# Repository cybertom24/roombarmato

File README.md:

# roombarmato

A repo to make a military version of the robotic vacuum cleaner Roomba

### TODO

#### PCB

- (OK) Posiziona fori di montaggio
- (OK) Trova valori per i condensatori del regolatore da 3.3V
- (OK) Controlla che il package dei componenti corrisponda
- (OK) Completa file ordine
- (OK) Modifica AK500
- (OK) Controlla funzionamento amplificatore audio
- (OK) Piano di massa in bottom e piano +12V in top

#### Arduino code

- (OK ?) Risolvi problema del blocco per colpa dei messaggi
- (OK) Aggiungi stop automatico dopo 2 secondi di assenza di messaggi
- Aggiungi controllo tensione della batteria e blocco di tutto quando si scende sotto i ~10.5V
- Completa comandi
- (OK) Aggiungi sistema di sincronizzazione ESP-arduino

##### Funzionalità

- (OK) Apri/Chiudi coperchio
- (OK) Spegni canne con millis() e non delay()
- (OK) Muovi
- (OK) Spegni motori dopo tot secondi di assenza messaggi
- (OK) Spegni tutto con disconnessione
- (OK) Accendi/Spegni occhi
- (OK) Controllo musica
- (OK) Controllo livello batteria
- (OK) Invio errore di lancio (perchè coperchio chiuso)
- (OK) Invio errore troppi messaggi
- Messaggio multiplo per accensione canne
- (OK) Invio stato batteria
- (OK) Invio stato coperchio

### ESP code

- Aggiungi sistema di sincronizzazione
- Aggiungi sistema di mantenimento di messaggi in modo da inviarne uno per volta

#### App

(OK) Semplifica algoritmo di gestione potenza dei motori

### Help

#### Comandi git

- Per impacchettare i file modificati: git add .
- Per assegnare il nome: git commit -m "nome alla modifica"
- Per caricare su internet: git push

- Per scaricare: git pull

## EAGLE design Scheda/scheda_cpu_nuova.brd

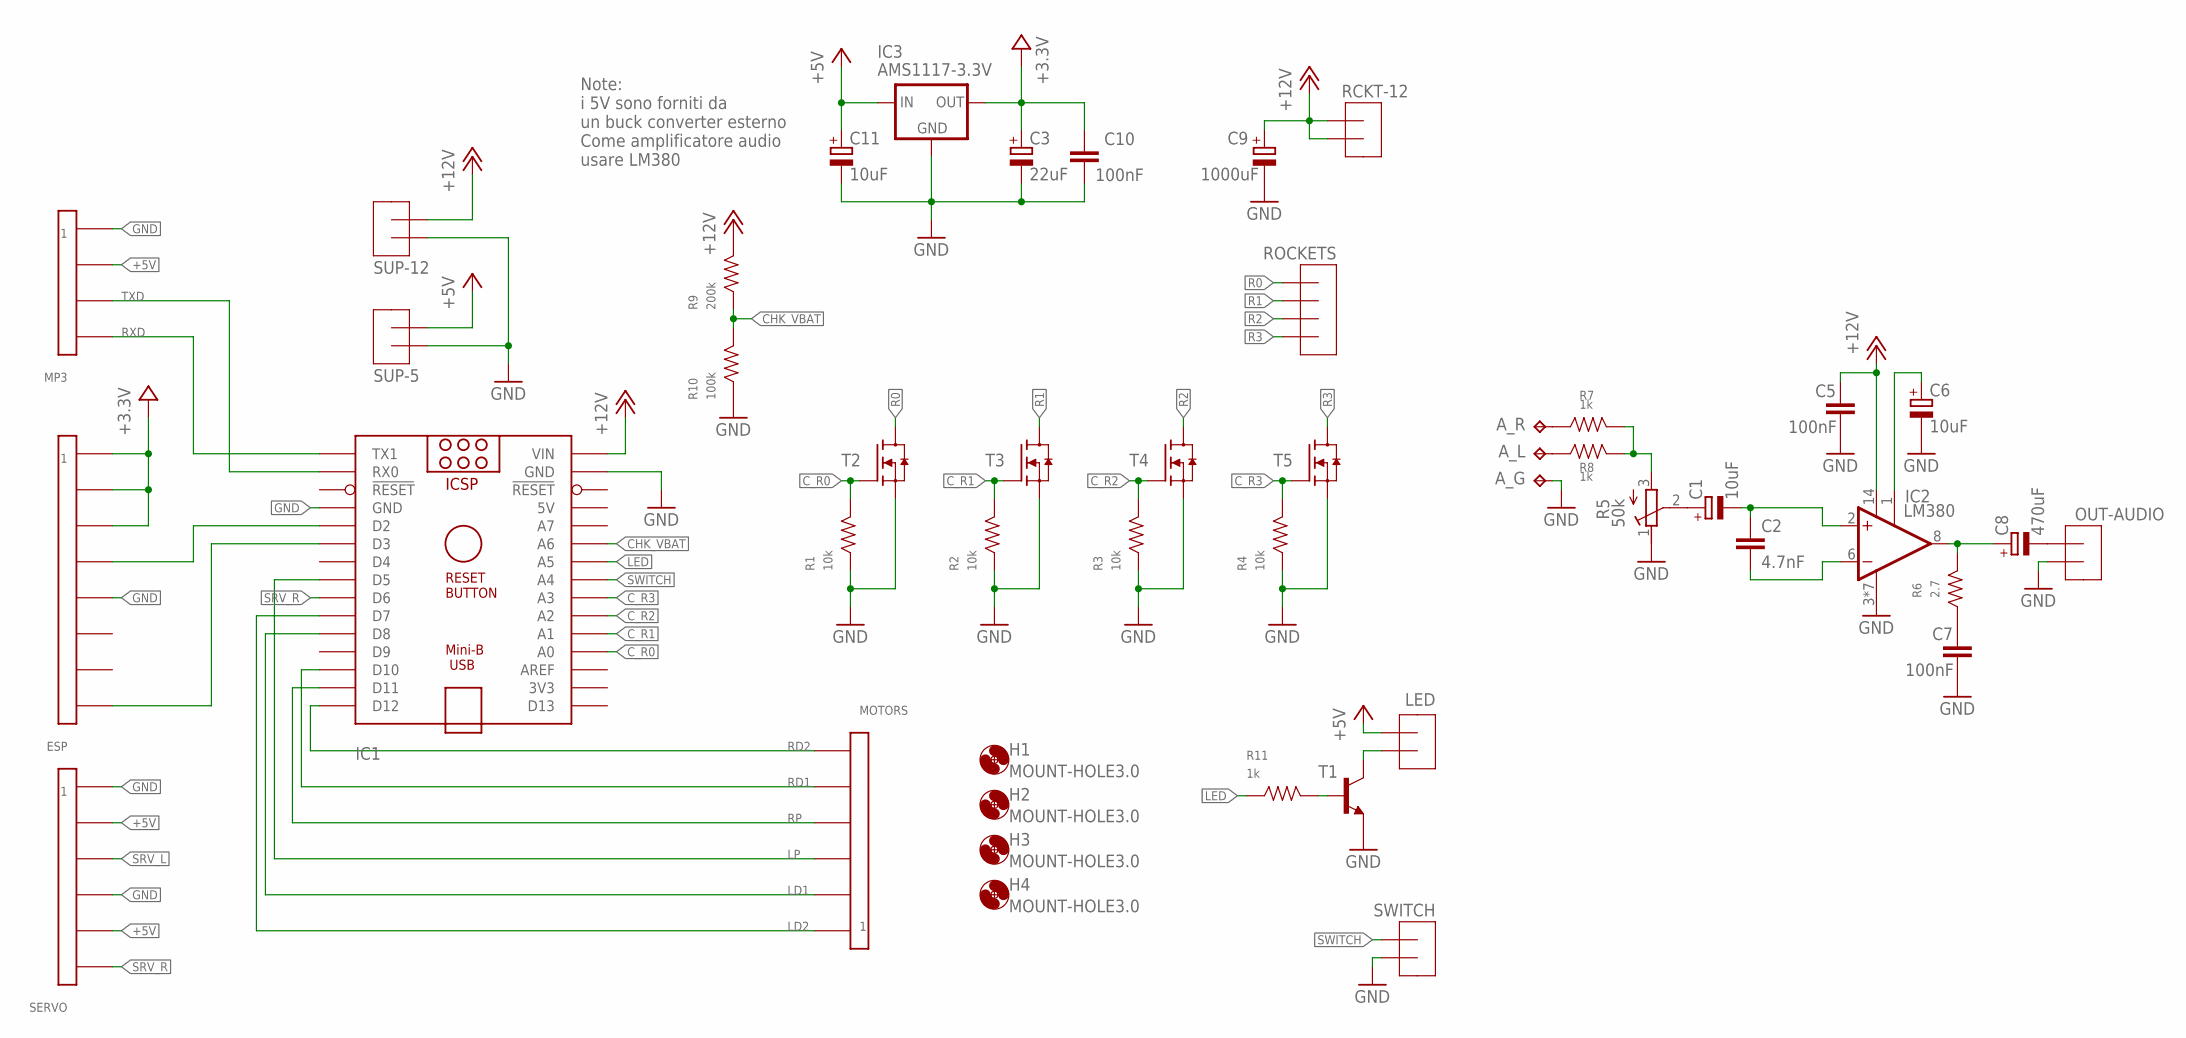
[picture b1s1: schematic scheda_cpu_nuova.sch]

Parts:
A_G: TPTP15SQ; TP15SQ
A_L: TPTP15SQ; TP15SQ
A_R: TPTP15SQ; TP15SQ
C1, C6, C11: 10uF; E2-4
C2: 4.7nF; C1206
C3: 22uF; E2-4
C5, C7, C10: 100nF; C1206
C8: 470uF; E3,5-8
C9: 1000uF; E3,5-10
ESP: CONNECTOR-82X4-CONNECTOR; 2X4-CONNECTOR
H1, H2, H3, H4: MOUNT-HOLE3.0; 3,0
IC1: ARDUINO-NANO; ARDUINO_NANO
IC2: LM380; DIL14
IC3: AMS1117-3.3V; SOT223
LED: MORSETTIERE-2
MOTORS: CONNECTOR-6; 1X6-CONNECTOR
MP3: CONNECTOR-4; 1X4-CONNECTOR
OUT-AUDIO: MORSETTIERE-2
R1, R2, R3, R4: 10k; 1206-RESISTOR
R5: 50k; RTRIM3314J
R6: 2.7; 1206-RESISTOR
R7, R8, R11: 1k; 1206-RESISTOR
R9: 200k; 1206-RESISTOR
R10: 100k; 1206-RESISTOR
RCKT-12: MORSETTIERE-2
ROCKETS: MORSETTIERE-4
SERVO: CONNECTOR-6; 1X6-CONNECTOR
SUP-5, SUP-12: MORSETTIERE-2
SWITCH: MORSETTIERE-2
T1: BC-817; SOT-23
T2, T3, T4, T5: MCU80N03A; D-PAK_TO252AA

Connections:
5V: IC1.12 (5V)
+3.3V: C3.+, C10.1, ESP.P$1, ESP.P$2, ESP.P$3, IC3.2 (OUT)
+5V: C11.+, IC3.3 (IN), LED.A, MP3.P$2, SERVO.P$2, SERVO.P$5, SUP-5.A
+12V: C5.1, C9.+, IC1.15 (VIN), IC2.14 (VSS), R9.P$2, RCKT-12.A, RCKT-12.B, SUP-12.A
CHK_VBAT: IC1.10 (A6), R9.P$1, R10.P$2
C_R0: IC1.4 (A0), R1.P$2, T2.1 (G)
C_R1: IC1.5 (A1), R2.P$2, T3.1 (G)
C_R2: IC1.6 (A2), R3.P$2, T4.1 (G)
C_R3: IC1.7 (A3), R4.P$2, T5.1 (G)
GND: A_G.TP, C3.-, C5.2, C6.-, C7.2, C9.-, C10.2, C11.-, ESP.P$5, IC1.14 (GND), IC1.19 (GND), IC2.3 (GND), IC2.4 (GND), IC2.5 (GND), IC2.7 (GND), IC2.10 (GND), IC2.11 (GND), IC2.12 (GND), IC3.1 (GND), MP3.P$1, OUT-AUDIO.A, R1.P$1, R2.P$1, R3.P$1, R4.P$1, R5.1 (E), R10.P$1, SERVO.P$1, SERVO.P$4, SUP-5.B, SUP-12.B, SWITCH.A, T1.P$1 (E), T2.3 (S), T3.3 (S), T4.3 (S), T5.3 (S)
IN_AUDIO: R5.3 (A), R7.P$2, R8.P$2
LD1: IC1.26 (D8), MOTORS.P$2
LD2: IC1.25 (D7), MOTORS.P$1
LED: IC1.9 (A5), R11.P$1
LP: IC1.23 (D5), MOTORS.P$3
unnamed: ESP.P$8, IC1.21 (D3)
unnamed: LED.B, T1.P$3 (C)
unnamed: R11.P$2, T1.P$2 (B)
unnamed: ESP.P$4, IC1.20 (D2)
unnamed: C1.+, R5.2 (S)
unnamed: C1.-, C2.1, IC2.2 (+IN)
unnamed: C2.2, IC2.6 (-IN)
unnamed: C6.+, IC2.1 (BYPASS)
unnamed: C7.1, R6.P$1
unnamed: C8.+, IC2.8 (OUT), R6.P$2
unnamed: C8.-, OUT-AUDIO.B
unnamed: A_R.TP, R7.P$1
unnamed: A_L.TP, R8.P$1
R0: ROCKETS.D, T2.4 (D)
R1: ROCKETS.C, T3.4 (D)
R2: ROCKETS.B, T4.4 (D)
R3: ROCKETS.A, T5.4 (D)
RD1: IC1.28 (D10), MOTORS.P$5
RD2: IC1.30 (D12), MOTORS.P$6
RP: IC1.29 (D11), MOTORS.P$4
RXD: IC1.16 (TX1), MP3.P$4
SRV_L: SERVO.P$3
SRV_R: IC1.24 (D6), SERVO.P$6
SWITCH: IC1.8 (A4), SWITCH.B
TXD: IC1.17 (RX0), MP3.P$3

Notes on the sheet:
Note: i 5V sono forniti da un buck converter esterno Come amplificatore audio usare LM380

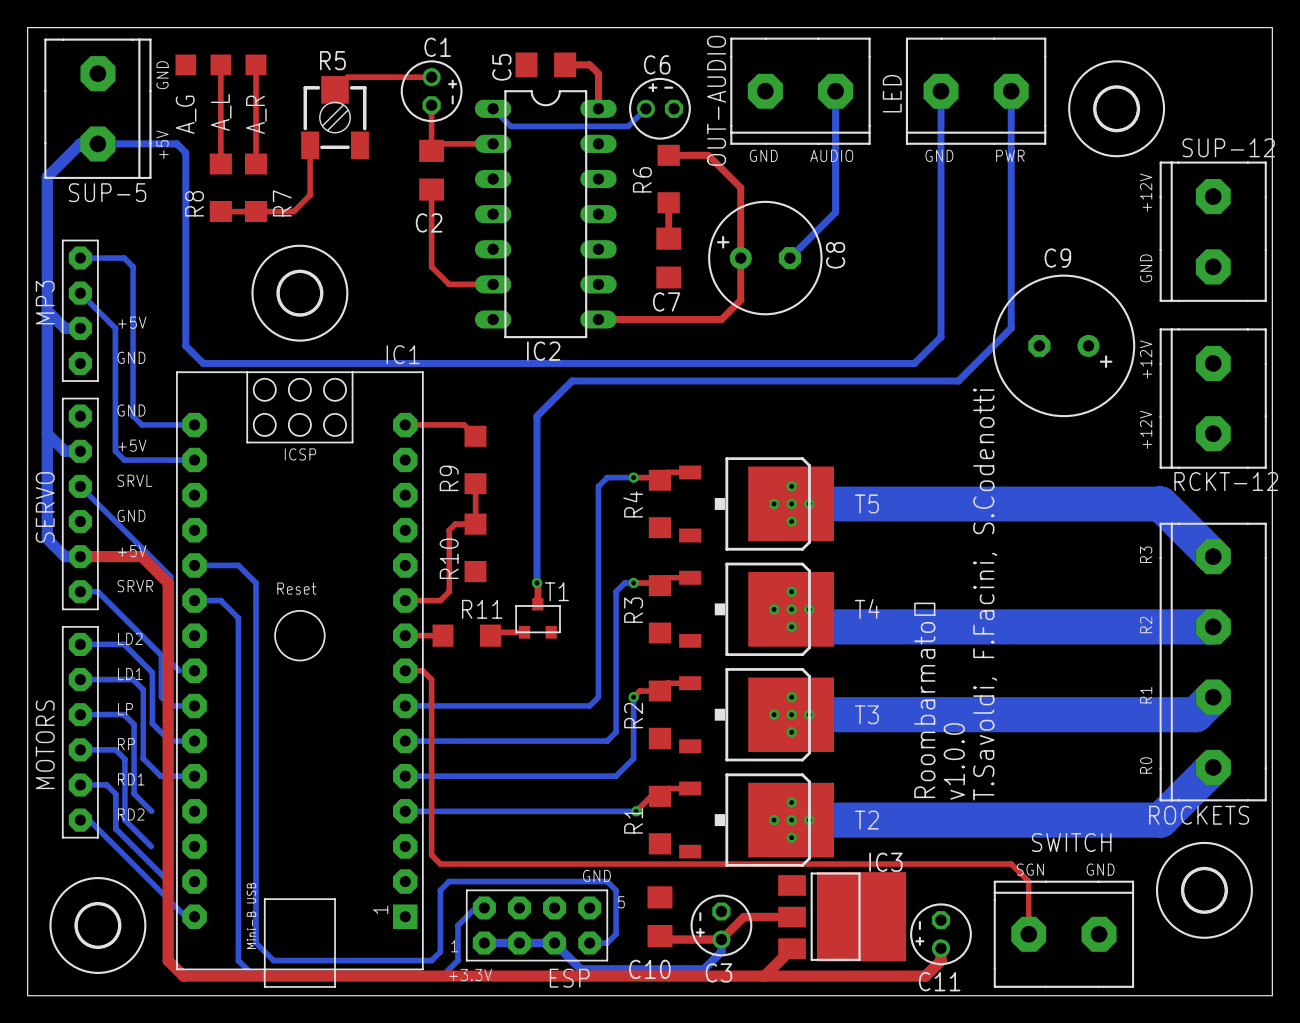
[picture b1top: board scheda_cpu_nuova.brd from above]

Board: 2 copper layers, 90.0 x 70.0 mm, 47 parts (0 on the bottom side), 38 nets.

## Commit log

2022-07-03 update with old files
2022-07-16 varie robe
2022-07-17 prova 2
2022-07-17 aggiunto cad canna per realizzazione prototipo n°2
2022-11-12 creata la libreria roombarmato_eagle_lib che verrà usata per tenere tutti i componenti presenti sulla scheda, aggiunti regolatori di tensione per la generazione di +5v e +3.3
2022-12-13 creato il pcb di prova
2023-01-14 modificato il sistema di accensione
2023-01-24 completato pcb con lm380
2023-01-24 creato file excel ordine
2023-01-25 aggiunta TODO in README.md
2023-01-25 Modificato TODO list in README
2023-01-25 aggiunte etichette su pcb
2023-01-25 aggiunti bat script per velocizzare push e pull
2023-02-10 create le cartelle test e ex
2023-02-28 modificato pcb
2023-03-11 modificato leggermente pcb, cambiato package lm380
2023-04-04 sistemato pcb
2023-04-04 quasi completato foglio ordine, da sistemare package condensatori (cambiare da 30x50 a 1206)
2023-04-05 sistemato pcb e ordine
2023-04-06 modificato todo
2023-04-06 completato PCB
2023-05-13 modificate varie robe
2023-05-13 modificati razzi
2023-06-04 modificati razzetti
2023-06-04 sistemata roba
2023-06-04 aggiunta file cad
2023-06-04 spostato cartella razzetti
2023-06-07 Sistemato progetti esp-code e arduino-code
2023-06-07 aggiunta libreria per TCP
2023-06-26 inseriti attacchi per servomotore e sistemato assembly finale sdw
2023-07-22 modifcato roba esp
2023-07-22 Crea cartella RoombaCode
2023-07-23 sistemato crash esp
2023-07-24 esp pronto all'uso; aggiunto funzioni ad arduino
2023-07-24 rimosso joystick_support (inutile)
2023-07-24 creato file algoritmo per code
2023-07-24 ampliato arduino-code
2023-07-24 creato file contenente tutti i comandi
2023-07-25 piccola modifica
2023-07-26 sistemato problema PWM
2023-07-27 modificato esp code
2023-07-27 Boh 5
2023-07-28 provando a sistemare comunicazione esp-arduino
2023-08-02 aggiungendo ECC alla comunicazione ESP-Arduino
2023-08-02 perSavo
2023-08-03 creando SecureSerial
2023-08-03 completando SecureSerial
2023-08-14 tentativi per migliorare connessione esp-arduino
2023-08-14 completando arduino-code
2023-08-15 sistemati codici
2023-08-17 problemi con i servo
2023-08-17 Boh 9
2023-08-17 varie cose
2023-08-23 aggiunto client
2023-09-02 creata cartella elementi strutturali in cad files, creato supporto per tenere fissa la batteria
2023-11-22 boh10
2024-02-10 roba varia
2024-10-10 altra roba
